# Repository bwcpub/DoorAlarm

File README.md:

# DoorAlarm

## KiCad schematic and PCB layout for my Freezer Door Alarm circuit - https://www.youtube.com/watch?v=F170j7Ktr-4 

**(C) 2021 Ben Cantrick. These files are distributed under a Creative Commons Attribution-ShareAlike license, see LICENSE.TXT.**

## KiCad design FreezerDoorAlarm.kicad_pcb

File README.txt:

KiCad schematic and PCB layout for my Freezer Door Alarm circuit.

For a full description of the circuit's design, and a simulation,
please see: https://www.youtube.com/watch?v=F170j7Ktr-4

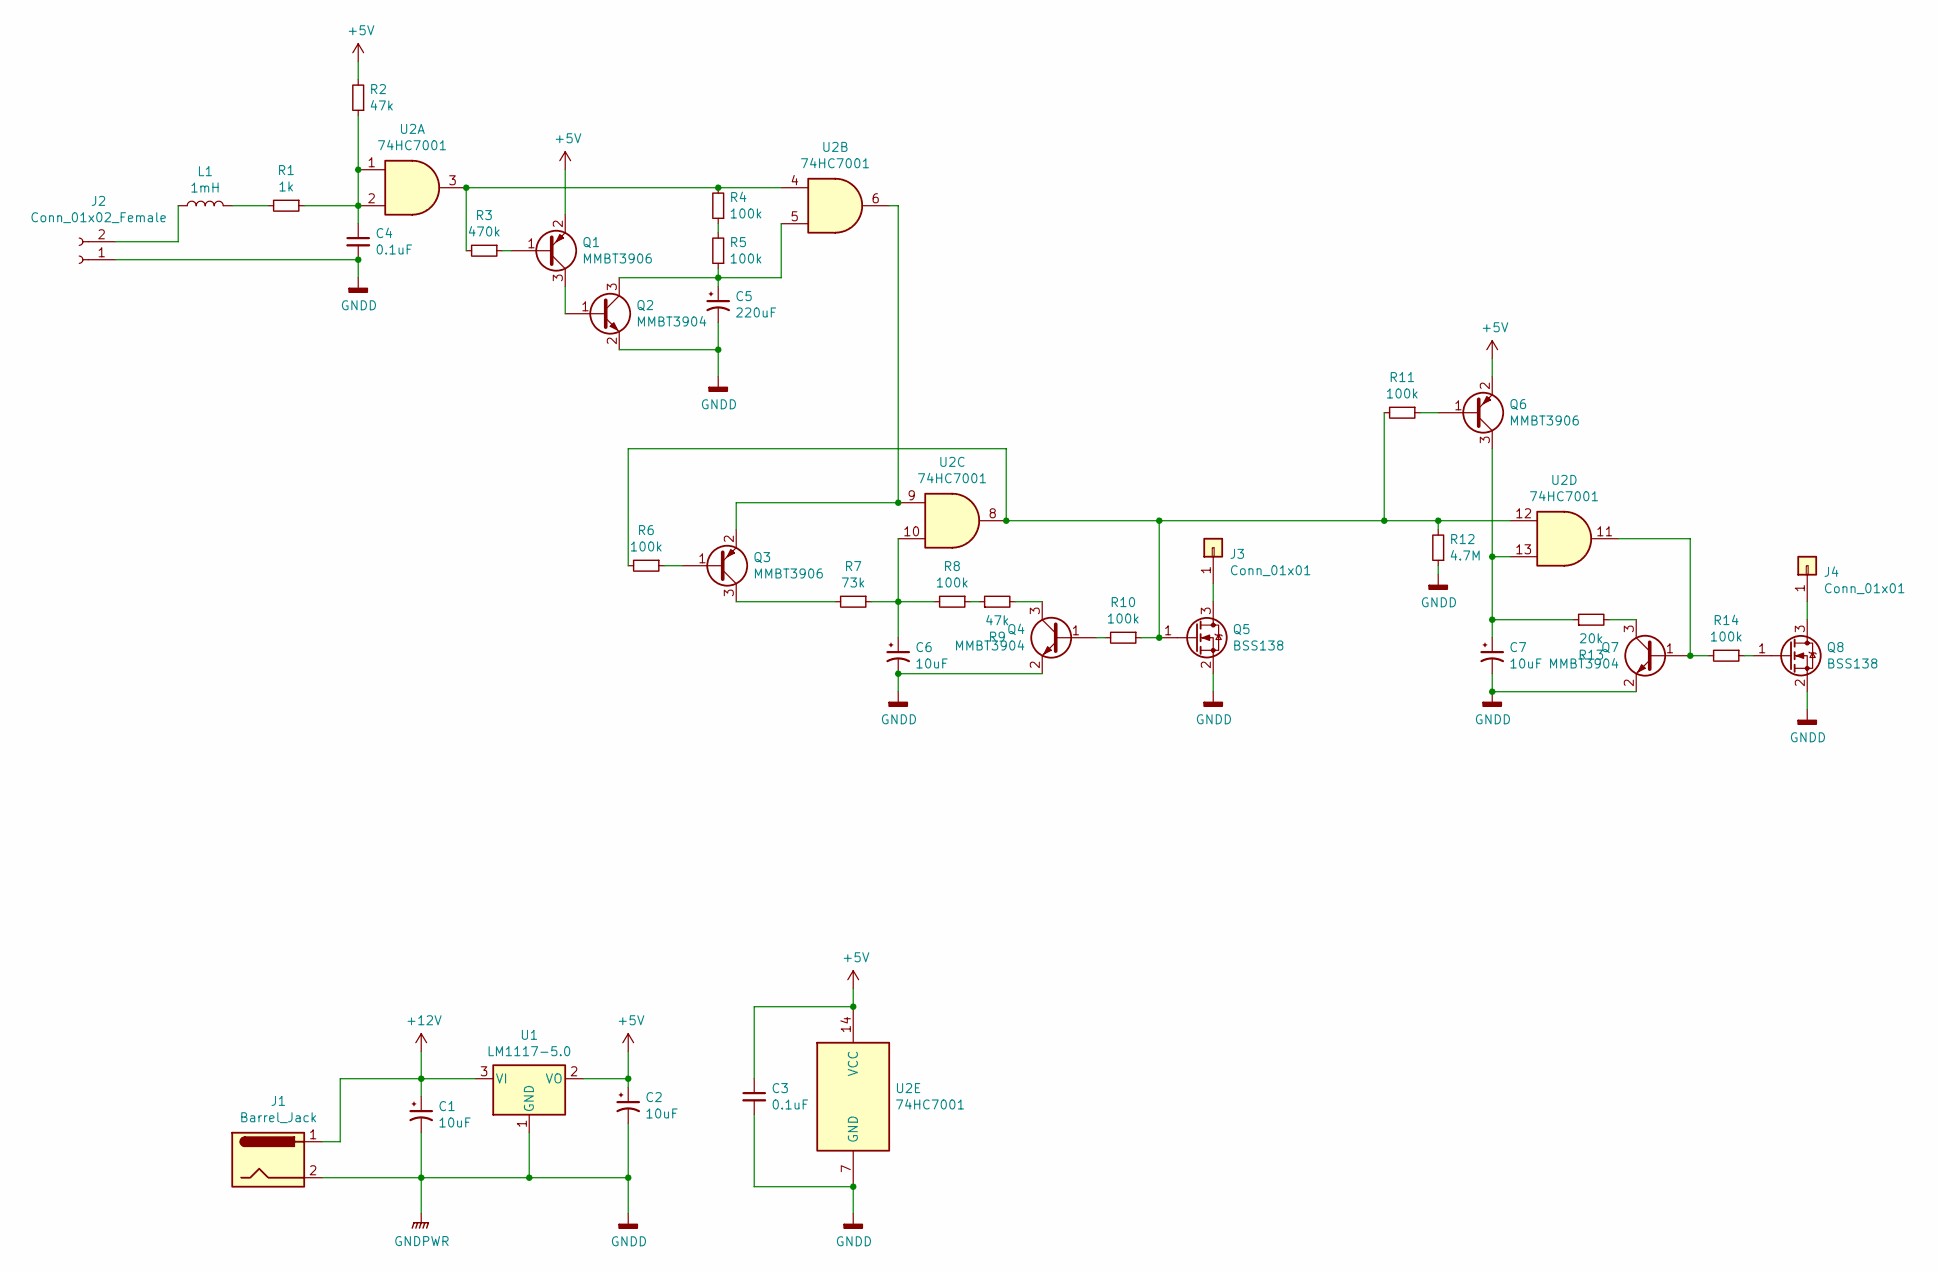
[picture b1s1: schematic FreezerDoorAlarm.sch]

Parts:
C1, C2, C6, C7: 10uF; CP_EIA-3528-15_AVX-H_Pad1.50x2.35mm_HandSolder
C3, C4: 0.1uF; C_0603_1608Metric_Pad1.08x0.95mm_HandSolder
C5: 220uF; CP_EIA-3528-15_AVX-H_Pad1.50x2.35mm_HandSolder
J1: Barrel_Jack; BarrelJack_CUI_PJ-036AH-SMT_Horizontal
J2: Conn_01x02_Female; TerminalBlock_Phoenix_MKDS-1,5-2-5.08_1x02_P5.08mm_Horizont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
J3, J4: Conn_01x01; TestPoint_Pad_4.0x4.0mm
L1: 1mH; L_Vishay_IHSM-4825
Q1, Q3, Q6: MMBT3906; SOT-23
Q2, Q4, Q7: MMBT3904; SOT-23
Q5, Q8: BSS138; SOT-23
R1: 1k; R_0603_1608Metric_Pad0.98x0.95mm_HandSolder
R2, R9: 47k; R_0603_1608Metric_Pad0.98x0.95mm_HandSolder
R3: 470k; R_0603_1608Metric_Pad0.98x0.95mm_HandSolder
R4, R5, R6, R8, R10, R11, R14: 100k; R_0603_1608Metric_Pad0.98x0.95mm_HandSolder
R7: 73k; R_0603_1608Metric_Pad0.98x0.95mm_HandSolder
R12: 4.7M; R_0603_1608Metric_Pad0.98x0.95mm_HandSolder
R13: 20k; R_0603_1608Metric_Pad0.98x0.95mm_HandSolder
U1: LM1117-5.0; SOT-223-3_TabPin2
U2: 74HC7001; SOIC-14_3.9x8.7mm_P1.27mm

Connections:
+5V: C2.1, C3.1, Q1.2 (E), Q6.2 (E), R2.2, U1.2 (VO), U2.14 (VCC)
+12V: C1.1, J1.1, U1.3 (VI)
GNDD: C1.2, C2.2, C3.2, C4.2, C5.2, C6.2, C7.2, J1.2, J2.1, Q2.2 (E), Q4.2 (E), Q5.2 (S), Q7.2 (E), Q8.2 (S), R12.1, U1.1 (GND), U2.7 (GND)
unnamed: C4.1, R1.1, R2.1, U2.1, U2.2
unnamed: C5.1, Q2.3 (C), R5.1, U2.5
unnamed: C6.1, R7.1, R8.2, U2.10
unnamed: C7.1, Q6.3 (C), R13.1, U2.13
unnamed: J2.2, L1.1
unnamed: J3.1, Q5.3 (D)
unnamed: J4.1, Q8.3 (D)
unnamed: L1.2, R1.2
unnamed: Q1.1 (B), R3.1
unnamed: Q1.3 (C), Q2.1 (B)
unnamed: Q3.1 (B), R6.1
unnamed: Q3.2 (E), U2.6, U2.9
unnamed: Q3.3 (C), R7.2
unnamed: Q4.1 (B), R10.2
unnamed: Q4.3 (C), R9.2
unnamed: Q5.1 (G), R6.2, R10.1, R11.2, R12.2, U2.8, U2.12
unnamed: Q6.1 (B), R11.1
unnamed: Q7.1 (B), R14.2, U2.11
unnamed: Q7.3 (C), R13.2
unnamed: Q8.1 (G), R14.1
unnamed: R3.2, R4.2, U2.3, U2.4
unnamed: R4.1, R5.2
unnamed: R8.1, R9.1

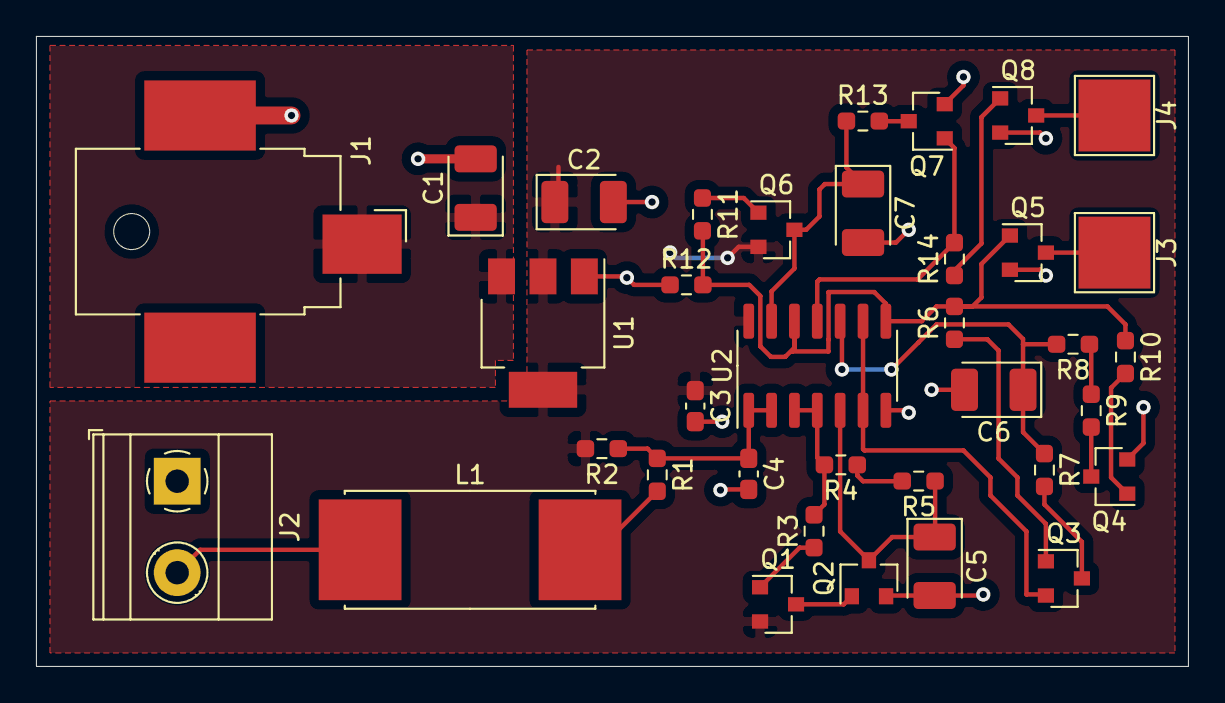
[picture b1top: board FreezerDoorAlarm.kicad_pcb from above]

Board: 2 copper layers, 64.0 x 35.0 mm, 36 parts (0 on the bottom side), 26 nets.

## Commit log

2021-07-17 Adding all files
2021-07-17 Fixing GitHub's incorrect auto-generated quotes.
2021-07-18 Where large/fast currents are expected to flow (Q2/C5, U2 bypass) loop area has been reduced.
